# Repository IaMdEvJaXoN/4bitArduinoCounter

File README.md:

# 4-Bit Arduino_Uno_R3 Binary Counter (Hardware & Firmware)

**Author:** Jackson  Asiligwa
**Status:** Completed Proof of Concept

This project demonstrates a full-stack embedded hardware design for a 4-bit binary counter using arduino uno R3, complete with an I2C LCD readout and discrete LED indicators. 

## Tech Stack
* **Firmware:** C++, PlatformIO, Arduino Framework
* **Hardware Design:** KiCad 8 (Schematic Capture & PCB Layout)
* **Simulation:** Wokwi in VS Code.
                  diagram.json in Wokwi web

## Simulation & Logic Verification
The logic and firmware were verified using the Wokwi simulator before routing physical hardware. The simulation verifies the 4-bit counting logic across the digital output pins and I2C text rendering.

## Hardware Design
The PCB acts as a custom carrier board (shield) for the Arduino Uno R3. It features standard 2.54mm headers for an I2C LCD backpack and utilizes through-hole (THT) resistors for LED current limiting.

## How to Run Locally
1. Clone this repository.
2. Open the folder in VS Code with the PlatformIO extension installed.
3. To view the simulation, install the Wokwi extension,get the commnunity licence(it's easy and fast-less than 10 seconds), open `diagram.json` file in the root folder, and start the simulator.

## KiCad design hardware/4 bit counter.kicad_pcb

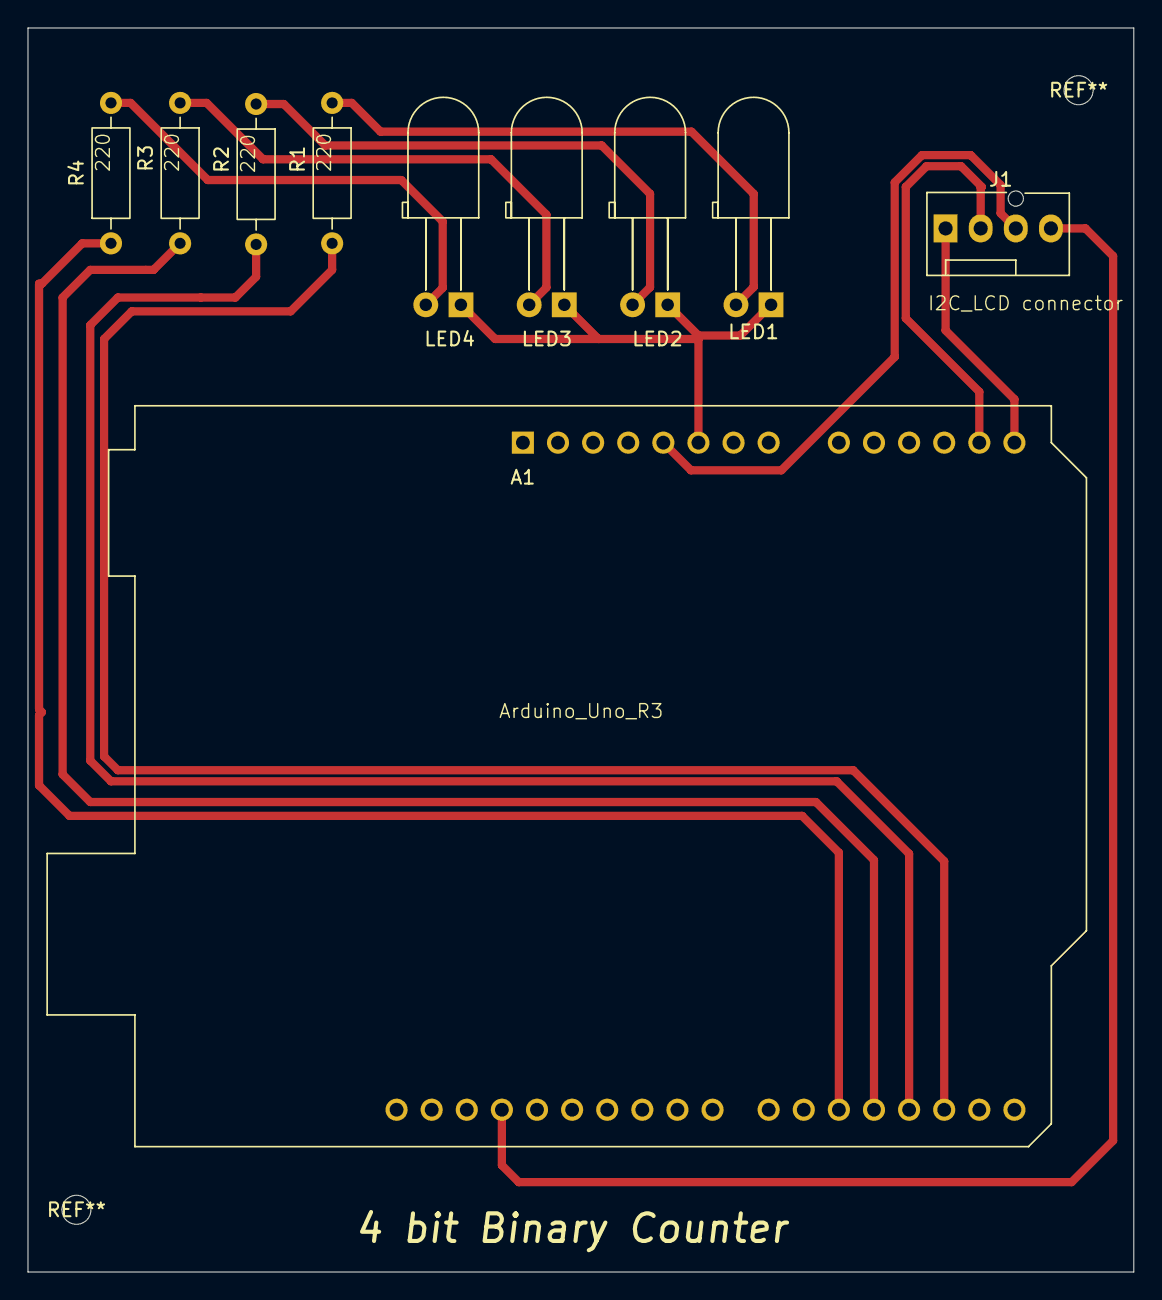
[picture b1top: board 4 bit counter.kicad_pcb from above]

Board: 2 copper layers, 80.0 x 90.0 mm, 10 parts (0 on the bottom side), 13 nets.

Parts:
A1: Arduino_UNO_R3
J1: Conn_01x04_Pin; FanPinHeader_1x04_P2.54mm_Vertical
LED1, LED2, LED3, LED4: LED; LED_D5.0mm_Horizontal_O6.35mm_Z15.0mm
R1, R2, R3, R4: 220; R_Axial_DIN0207_L6.3mm_D2.5mm_P10.16mm_Horizontal

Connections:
unnamed: A1.5 (+5V), J1.3
unnamed: A1.17 (D2), R1.2
unnamed: A1.18 (D3), R2.2
unnamed: A1.19 (D4), R3.2
unnamed: A1.20 (D5), R4.1
unnamed: LED1.2 (A), R1.1
unnamed: A1.6 (GND), LED1.1 (K), LED2.1 (K), LED3.1 (K), LED4.1 (K)
unnamed: LED2.2 (A), R2.1
unnamed: LED3.2 (A), R3.1
unnamed: LED4.2 (A), R4.2
unnamed: A1.14 (SCL/A5), J1.1
unnamed: A1.13 (SDA/A4), J1.2
unnamed: A1.29 (GND), J1.4
